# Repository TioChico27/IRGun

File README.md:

Lightgun4IR

Projeto original: https://github.com/yakaracolombia/IRGun_Makoto_Yakarizado

Esta versão contém algumas modificações e correção de bugs.

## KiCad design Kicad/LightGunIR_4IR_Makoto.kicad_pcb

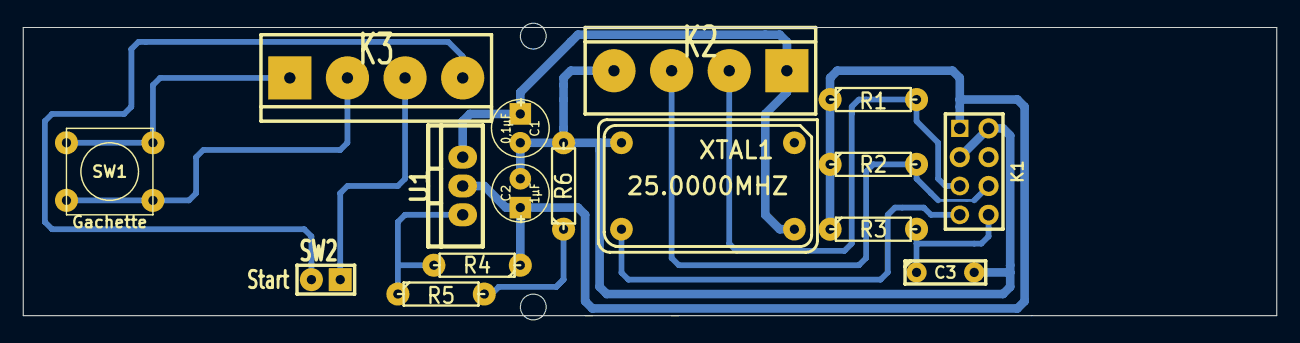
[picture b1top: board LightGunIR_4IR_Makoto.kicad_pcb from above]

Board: 2 copper layers, 110.5 x 26.1 mm, 16 parts (0 on the bottom side), 13 nets.

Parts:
C1: 0,1µF; C1V5
C2: 1µF; C1V5
C3: 100nF; C2
K1: CONN_4X2; pin_array_4x2
K2, K3: CONN_4; bornier4
R1, R2: 2,2k; R3
R3: 22k; R3
R4: 240; R3
R5: 300; R3
R6: 100; R3
SW1: Gachette; SW_PUSH_SMALL
SW2: Start; SIL-2
U1: LM317T; TO-220_Neutral123_Vertical
XTAL1: 25.0000MHZ; XO-14S

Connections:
+3.3V: C2.1, K1.1, R1.1, R2.1, R3.1, R4.1, U1.2
+5V: C1.1, K2.1, U1.3, XTAL1.14
/SCL: K1.5, K2.2, R1.2
/SDA: K1.6, K2.3, R2.2
GND: C1.2, C2.2, C3.2, K1.2, K1.3, K2.4, R6.2, XTAL1.7
unnamed: C3.1, K1.8, R3.2
unnamed: K1.7, XTAL1.8
unnamed: K3.4, SW2.2
unnamed: K3.1, SW1.1
unnamed: K3.2, SW1.2
unnamed: K3.3, SW2.1
unnamed: R5.2, R6.1
unnamed: R4.2, R5.1, U1.1

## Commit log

2023-03-11 Create Kicad
2023-03-11 Create test
2023-10-12 primer lanzamiento
2023-10-12 app
    se agrgaron dos versiones de la app de test y el diagrama de la camara de wii
2023-10-12 Update README.md
    traduccion del readme
2023-10-13 update previo a lanzamiento del video
    demasiadas modificaciones a la aplicacion de testeo, donde ahora se coloca un selector de puerto COM ademas de mapear los 6 botones de la ir gun
    Tabien se agrego test de luz led, tanto para el led rgb como para el led que emite el boton de disparo
2023-10-20 Update TEST_MAKOTO_RGB.ino
    se actualiza el codigo de test para que tambien haga prueba del solenoide al pin A10
2023-10-20 Update LightGunIR_4IR_Makoto_V2.4.ino
    correccion de offset despues de lectura de eeprom
2023-10-20 traduccion de los comentarios
    Traduccion completa del los comentarios del codigo para facilitar su entendimiento
2023-10-20 readme
    correccion explicacion para calibrar
2023-11-02 sync
2023-11-07 fix windows 10
2023-11-08 Create SOLENOIDE IR GUN.png
    se agrega imagen del diagrama de solenoide
2023-12-14 SE AGREGO UNA VERSION QUE INCLUYE JAVA
2023-12-14 java source
2023-12-14 source fix
